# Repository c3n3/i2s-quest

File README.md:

# i2s-quest
We making an i2s thingy

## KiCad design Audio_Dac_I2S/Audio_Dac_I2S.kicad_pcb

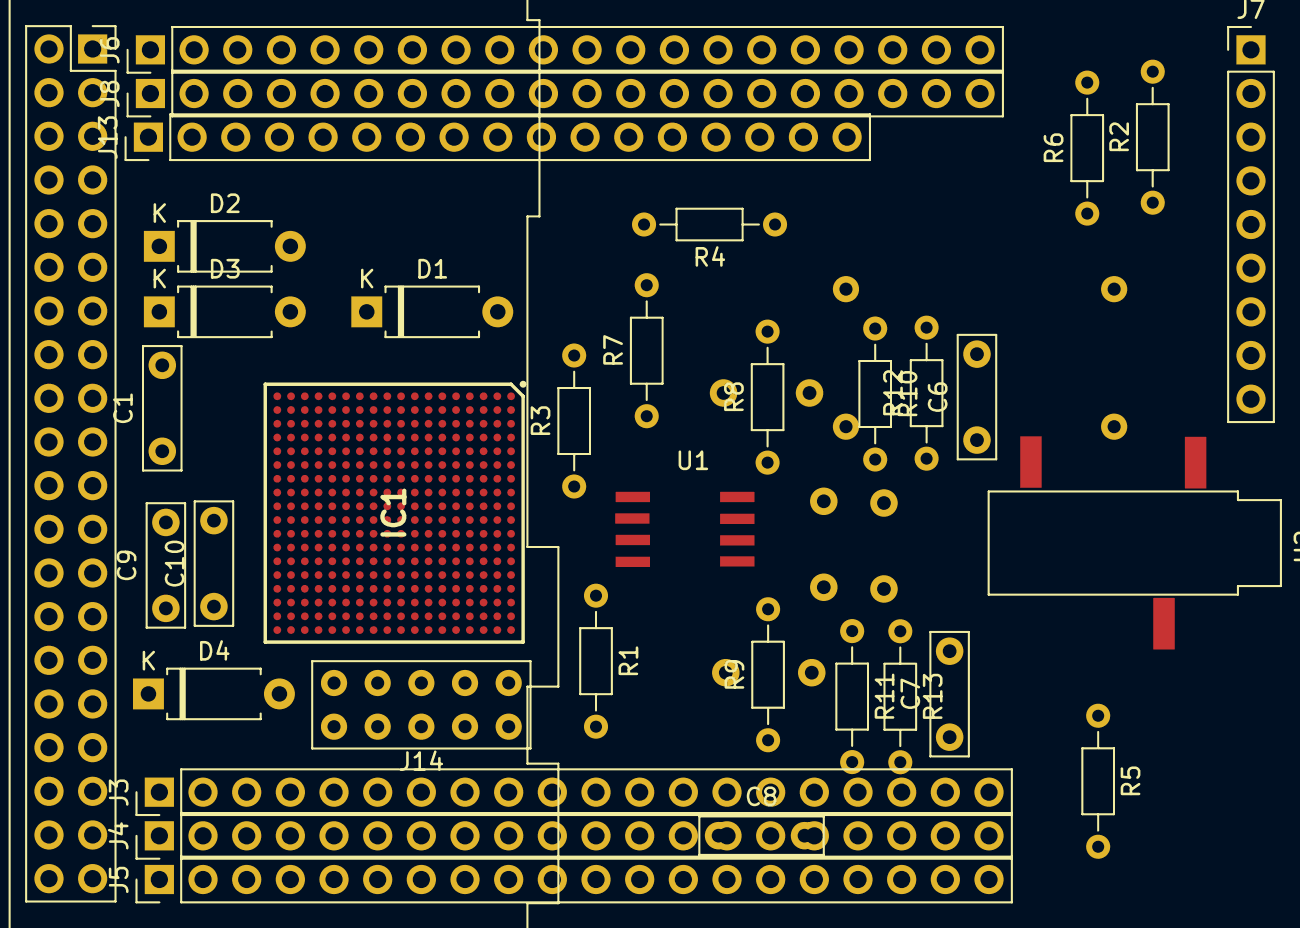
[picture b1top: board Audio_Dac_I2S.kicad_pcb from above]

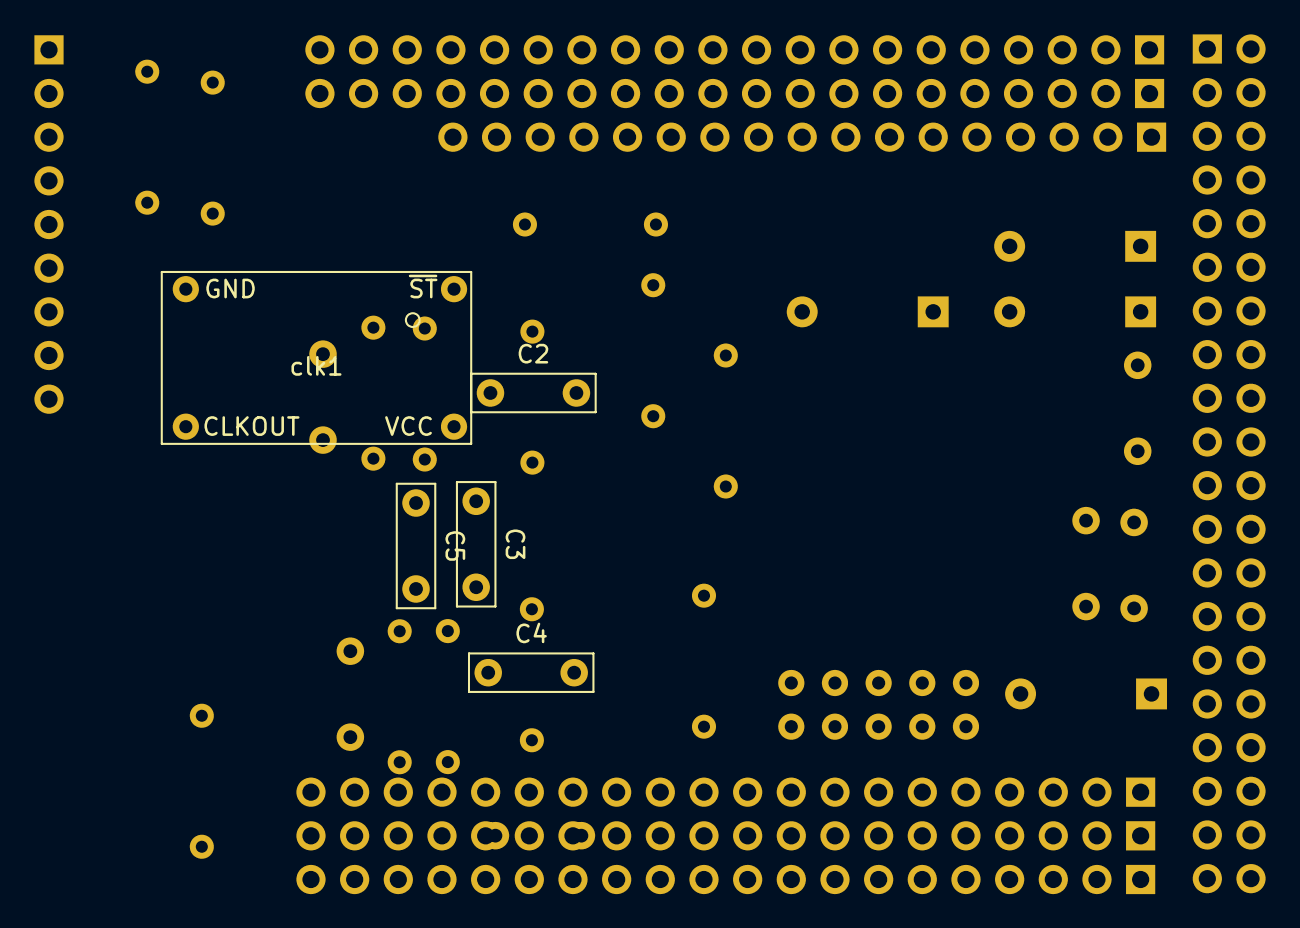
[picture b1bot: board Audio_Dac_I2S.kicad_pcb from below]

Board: 4 copper layers, 40 parts (5 on the bottom side), 111 nets, no tracks yet.

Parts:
C1, C8, C9, C10: 10pF; C_Rect_L7.0mm_W2.0mm_P5.00mm
C2, C4: 3.3uF; C_Rect_L7.0mm_W2.0mm_P5.00mm
C3: 0.1u; C_Rect_L7.0mm_W2.0mm_P5.00mm
C5: 1u; C_Rect_L7.0mm_W2.0mm_P5.00mm
C6, C7: C; C_Rect_L7.0mm_W2.0mm_P5.00mm
D1, D2, D3, D4: DIODE; D_A-405_P7.62mm_Horizontal
IC1: 10M02DCU324A7G; BGA324C80P18X18_1500X1500X155
J1: Raspberry_Pi_2_3; Raspberry_Pi_40_pin_socket
J3, J4, J5, J6, J8: Conn_01x20_Male; PinHeader_1x20_P2.54mm_Vertical
J7: Conn_01x09_Male; PinHeader_1x09_P2.54mm_Vertical
J13: Conn_01x17_Male; PinHeader_1x17_P2.54mm_Vertical
J14: AVR-JTAG-10; Jtag_header
R1, R2, R3, R4, R5, R6, R7, R10, R11: 10K; R_Axial_DIN0204_L3.6mm_D1.6mm_P7.62mm_Horizontal
R8, R9: 267K; R_Axial_DIN0204_L3.6mm_D1.6mm_P7.62mm_Horizontal
R12, R13: 560; R_Axial_DIN0204_L3.6mm_D1.6mm_P7.62mm_Horizontal
U1: DAC
U2: FemaleAudioJack; Audio_Jack
clk1: tco-711AR; tco-711

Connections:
5Vin: C3.2, C5.2, U1.7
CLK: IC1.M3, clk1.3
DATA: IC1.A3, J1.40
DCLK: IC1.A2, J1.22
EN: IC1.A5, J1.16
GND: C1.2, C3.1, C5.1, C6.2, C7.1, C8.2, C9.2, C10.2, IC1.A1, IC1.A18, IC1.B6, IC1.B10, IC1.B15, IC1.D3, IC1.E6, IC1.E10, IC1.E13, IC1.F8, IC1.F17, IC1.G2, IC1.G4, IC1.H14, IC1.J10, IC1.J17, IC1.K6, IC1.K9, IC1.K13, IC1.L4, IC1.M14, IC1.N2, IC1.N5, IC1.N10, IC1.N12, IC1.N17, IC1.R7, IC1.U4, IC1.U10, IC1.U14, IC1.V1, IC1.V18, J1.6, J1.9, J1.14, J1.20, J1.25, J1.30, J1.34, J1.39, J3.9, J4.1, J4.5, J4.6, J4.14, J5.1, J5.3, J5.5, J6.13, J7.5, J7.8, J8.6, J8.9, J8.13, J13.4, J13.6, J13.7, J13.17, J14.2, R1.2, R3.2, R4.2, R8.1, R9.2, R10.2, R11.1, U1.6, U2.1, clk1.2
INTERR: IC1.A4, J1.18
LRCK: IC1.A8, U1.3
MCLK: IC1.A9, U1.4
unnamed: C2.1, R10.1, R12.2
unnamed: C2.2, R8.2, U1.8
unnamed: C4.1, R11.2, R13.2
unnamed: C4.2, R9.1, U1.5
unnamed: C6.1, R12.1, U2.2
unnamed: C7.2, R13.1, U2.3
unnamed: IC1.C5, J3.1
unnamed: IC1.C6, J3.2
unnamed: IC1.C7, J3.3
unnamed: IC1.C8, J3.4
unnamed: IC1.C9, J3.5
unnamed: IC1.C10, J3.6
unnamed: IC1.C17, J3.7
unnamed: IC1.C18, J3.8
unnamed: IC1.D4, J3.10
unnamed: IC1.D5, J3.11
unnamed: IC1.D6, J3.12
unnamed: IC1.D7, J3.13
unnamed: IC1.D8, J3.14
unnamed: IC1.D15, J3.15
unnamed: IC1.D16, J3.16
unnamed: IC1.D17, J3.17
unnamed: IC1.D18, J3.18
unnamed: IC1.E4, J3.19
unnamed: IC1.E5, J3.20
unnamed: IC1.E15, J4.7
unnamed: IC1.E16, J4.8
unnamed: IC1.E17, J4.9
unnamed: IC1.E18, J4.10
unnamed: IC1.F2, J4.11
unnamed: IC1.F5, J4.12
unnamed: IC1.F10, J4.16
unnamed: IC1.F13, J4.17
unnamed: IC1.F15, J4.19
unnamed: IC1.F16, J4.20
unnamed: IC1.F18, J5.2
unnamed: IC1.G3, J5.4
unnamed: IC1.G6, J5.7
unnamed: IC1.G7, J5.8
unnamed: IC1.G8, R6.1
unnamed: IC1.G9, R3.1
unnamed: IC1.G10, J5.11
unnamed: IC1.G11, J5.12
unnamed: IC1.G12, J5.13
unnamed: IC1.G15, J5.16
unnamed: IC1.G16, J5.17
unnamed: IC1.G17, J5.18
unnamed: IC1.G18, J5.19
unnamed: IC1.H1, J5.20
unnamed: IC1.H2, J6.1
unnamed: IC1.H6, J6.5
unnamed: IC1.H7, J6.6
unnamed: IC1.H8, R7.1
unnamed: IC1.H9, R2.1
unnamed: IC1.H10, J6.9
unnamed: IC1.H11, J6.10
unnamed: IC1.H12, J6.11
unnamed: IC1.H17, J6.14
unnamed: IC1.H18, J6.15
unnamed: IC1.J1, J6.16
unnamed: IC1.J2, J6.17
unnamed: IC1.J3, J6.18
unnamed: IC1.J4, J6.19
unnamed: IC1.J6, J7.1
unnamed: IC1.J9, J7.4
unnamed: IC1.J18, J7.9
unnamed: IC1.K1, J8.1
unnamed: IC1.K2, J8.2
unnamed: IC1.K3, J8.3
unnamed: IC1.K4, J8.4
unnamed: IC1.K7, J8.7
unnamed: IC1.K8, J8.8
unnamed: IC1.K10, J8.10
unnamed: IC1.K11, J8.11
unnamed: IC1.K12, J8.12
unnamed: IC1.K15, J8.15
unnamed: IC1.K16, J8.16
unnamed: IC1.K17, J8.17
unnamed: IC1.K18, J8.18
unnamed: IC1.L1, J8.19
unnamed: IC1.L2, J8.20
unnamed: IC1.U7, J13.1
unnamed: IC1.U8, J13.2
unnamed: IC1.U9, J13.3
unnamed: IC1.U11, J13.5
unnamed: IC1.V2, J13.8
unnamed: IC1.V3, J13.9
unnamed: IC1.V4, J13.10
unnamed: IC1.V5, J13.11
unnamed: IC1.V6, J13.12
unnamed: IC1.V7, J13.13
unnamed: IC1.V8, J13.14
unnamed: IC1.V9, J13.15
unnamed: IC1.V12, J13.16
unnamed: R1.1, U1.2
SDATA: IC1.A6, U1.1
V3.3: D1.2, D2.2, D3.2, D4.2, IC1.E8, IC1.E9, IC1.F6, IC1.F9, IC1.F14, IC1.G5, IC1.G13, IC1.G14, IC1.H5, IC1.H13, IC1.J5, IC1.J13, IC1.J14, IC1.K5, IC1.K14, IC1.L5, IC1.L6, IC1.L13, IC1.L14, IC1.M5, IC1.M6, IC1.M13, IC1.N9, IC1.P7, IC1.P8, IC1.P9, IC1.P13, J1.17, J4.3, J4.4, J4.13, J4.15, J4.18, J5.6, J5.9, J5.14, J5.15, J6.4, J6.7, J6.12, J6.20, J7.6, J7.7, J8.5, J8.14, J14.4, R2.2, R5.2, R6.2, R7.2, clk1.4
VCCIO_B8: IC1.E7, J4.2
tck: C1.1, D1.1, IC1.J8, J7.3, J14.1, R4.1
tdi: C9.1, D3.1, IC1.H3, J6.2, J14.9
tdo: C8.1, D2.1, IC1.H4, J6.3, J14.3
tms: C10.1, D4.1, IC1.J7, J7.2, J14.5

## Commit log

2021-10-20 start of the arduino project
2021-10-21 Got sine wave thing done
2021-10-21 Arduino.h
2021-10-27 Added stuff
2021-10-28 added some parts to the pcb design
2021-11-04 got more done on footprints and circuit schematic
2021-11-11 updated schematics and footprints
2021-11-17 making progress on PCB
2021-11-17 verilog
2021-11-18 The driver has all the ground work
2021-11-18 made schematic updates
2021-11-18 Added clock symbol and footprint
2021-11-18 dded label
2021-11-18 editted fpga symbol and made jtag footprint
2021-11-18 hopefully finished schematic
2021-11-18 laying out the PCB
2021-11-19 Done
2021-11-29 UPdated driver to output everything
2021-11-29 Added clock lines
2021-12-02 PI driver
2021-12-02 fpga not sending interrupt
2021-12-06 interrupt being sent
2021-12-08 Made pi clock better
2021-12-08 Made it better
2021-12-08 Made even better
2021-12-08 More++
2021-12-08 not working
2021-12-08 More++++
2021-12-09 More+++++
2021-12-09 broken
2021-12-09 More+++++++++
2021-12-09 stuff
2021-12-11 data clk bad
2021-12-11 sawtooth
2021-12-11 More driver stuff
2021-12-11 dec 11 start
2021-12-11 More++++++++++++
2021-12-11 More+++++++++++++++++++
2021-12-11 Better--
2021-12-11 no negedge/posedge always blocks
2021-12-11 Golden ticket
2021-12-11 Vs code
2021-12-11 More
2021-12-11 This is stupid
2021-12-11 More++++++++++++++++++++++++++++++++
2021-12-11 More++++++++++++++++++++++++++++++++++++++++++++++++++++++++++++++++
2021-12-11 More+++++++++++++++++++++++++++++++++++++++++++++++++++++++++++++++++++++++++++++++++++++++
2021-12-11 More+++++++++++++++++++++++++++++++++++++++++++++++++++++++++++++++++++++++++++++++++++++++++++++++++++++++++++++++++++++++++++++++
2021-12-13 Cleaned code
2021-12-14 comments
